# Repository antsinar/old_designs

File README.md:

Some old designs i made following tutorials online.
All KiCad projects.
The first one is a Charlie plexing keychain with a 2032 battery holder.
The second one was originally an alarm clock idea that simulated sunrise and sunset with a stackable design. (if ordered from JLCPCB, you would have one full set)
Do whatever you want with them.

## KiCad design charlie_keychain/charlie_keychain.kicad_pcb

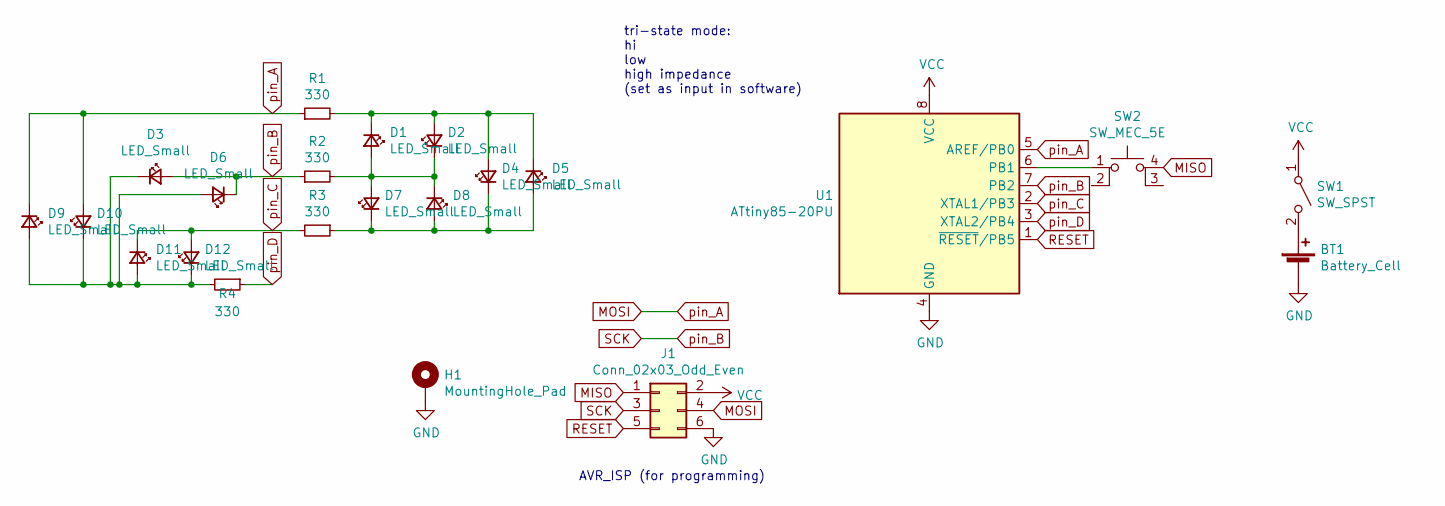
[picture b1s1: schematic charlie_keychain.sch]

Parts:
BT1: Battery_Cell; BatteryHolder_Keystone_1060_1x2032
D1, D2, D3, D4, D5, D6, D7, D8, D9, D10, D11, D12: LED_Small; LED_0805_2012Metric
H1: MountingHole_Pad; MountingHole_2.5mm_Pad_TopBottom
J1: Conn_02x03_Odd_Even; PinHeader_2x03_P2.00mm_Vertical
R1, R2, R3, R4: 330; R_0805_2012Metric
SW1: SW_SPST; SW_DIP_SPSTx01_Slide_Copal_CHS-01B_W7.62mm_P1.27mm
SW2: SW_MEC_5E; SW_SPST_Omron_B3FS-100xP
U1: ATtiny85-20PU; DIP-8_W7.62mm

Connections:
GND: BT1.2 (-), H1.1, J1.6, U1.4 (GND)
MISO: J1.1, SW2.4 (A)
MOSI: D9.1 (K), D10.2 (A), J1.4, R1.1, U1.5 (AREF/PB0)
unnamed: BT1.1 (+), SW1.2 (B)
unnamed: D1.1 (K), D2.2 (A), D4.2 (A), D5.1 (K), R1.2
unnamed: D1.2 (A), D2.1 (K), D7.2 (A), D8.1 (K), R2.2
unnamed: D4.1 (K), D5.2 (A), D7.1 (K), D8.2 (A), R3.1
unnamed: D3.1 (K), D6.2 (A), D9.2 (A), D10.1 (K), D11.2 (A), D12.1 (K), R4.2
unnamed: SW2.1, U1.6 (PB1)
RESET: J1.5, U1.1 (~RESET~/PB5)
SCK: D3.2 (A), D6.1 (K), J1.3, R2.1, U1.7 (PB2)
VCC: J1.2, SW1.1 (A), U1.8 (VCC)
pin_C: D11.1 (K), D12.2 (A), R3.2, U1.2 (XTAL1/PB3)
pin_D: R4.1, U1.3 (XTAL2/PB4)

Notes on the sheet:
tri-state mode: hi low high impedance (set as input in software)
AVR_ISP (for programming)

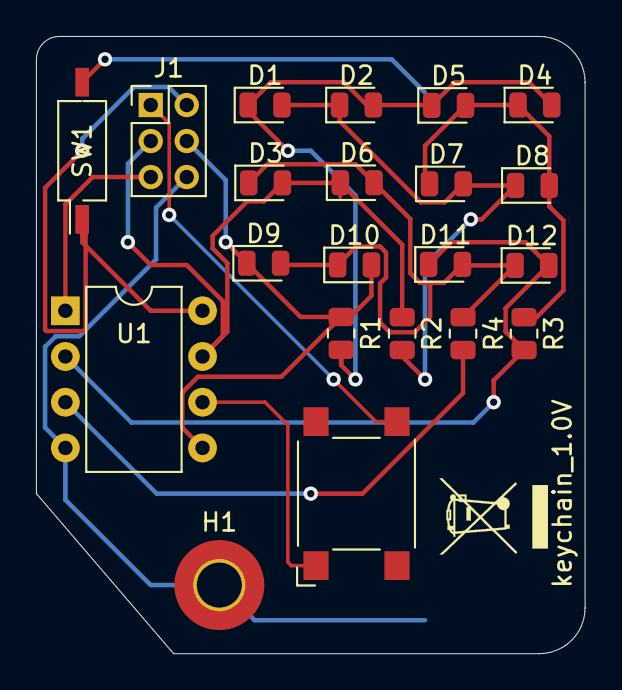
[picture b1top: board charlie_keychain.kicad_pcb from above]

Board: 2 copper layers, 30.5 x 34.3 mm, 22 parts (1 on the bottom side), 14 nets.

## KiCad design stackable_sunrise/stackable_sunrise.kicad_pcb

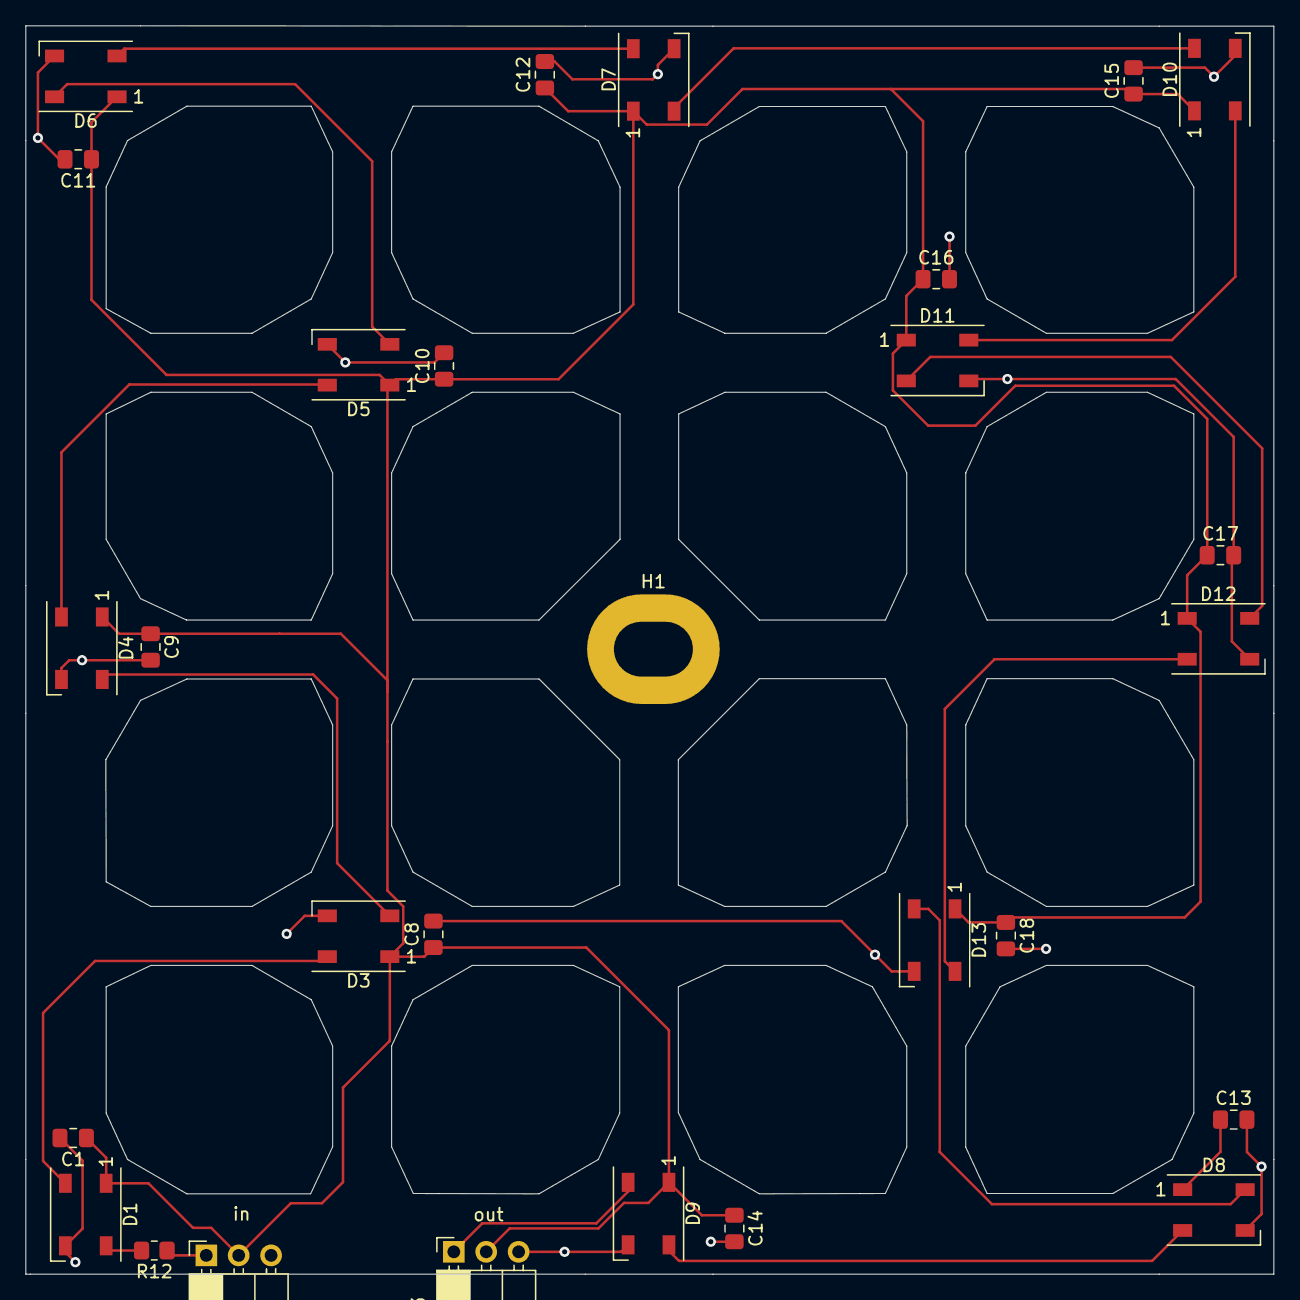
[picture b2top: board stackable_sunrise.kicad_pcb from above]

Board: 2 copper layers, 97.8 x 97.9 mm, 28 parts (0 on the bottom side), 16 nets.

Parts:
C1, C8, C9, C10, C11, C12, C13, C14, C15, C16, C17, C18: 100u; C_0805_2012Metric_Pad1.18x1.45mm_HandSolder
D1, D3, D4, D5, D6, D7, D8, D9, D10, D11, D12, D13: WS2812B; LED_WS2812B_PLCC4_5.0x5.0mm_P3.2mm
H1: MountingHole_Pad; MountingHole_4.3x6.2mm_M4_Pad
J2, J3: Conn_01x03; PinSocket_1x03_P2.54mm_Horizontal
R12: 330; R_0805_2012Metric_Pad1.20x1.40mm_HandSolder

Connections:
5v_next_layer: C1.1, C8.1, C9.1, C10.1, C11.1, C12.1, C13.1, C14.1, C15.1, C16.1, C17.1, C18.1, D1.1, D3.1, D4.1, D5.1, D6.1, D7.1, D8.1, D9.1, D10.1, D11.1, D12.1, D13.1, J2.2, J3.2
DIN: D1.4, R12.2
unnamed: D1.2, D3.4
unnamed: D3.2, D4.4
unnamed: D4.2, D5.4
unnamed: D5.2, D6.4
unnamed: D6.2, D7.4
unnamed: D8.2, D9.4
unnamed: D10.2, D11.4
unnamed: D7.2, D10.4
unnamed: D11.2, D12.4
unnamed: D12.2, D13.4
unnamed: D8.4, D13.2
unnamed: J2.1, R12.1
common_ground: C1.2, C8.2, C9.2, C10.2, C11.2, C12.2, C13.2, C14.2, C15.2, C16.2, C17.2, C18.2, D1.3, D3.3, D4.3, D5.3, D6.3, D7.3, D8.3, D9.3, D10.3, D11.3, D12.3, D13.3, H1.1, J2.3, J3.3
din_next_layer: D9.2, J3.1

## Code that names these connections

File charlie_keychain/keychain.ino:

#include <avr/sleep.h>
#define nop() asm volatile("nop")
boolean leds_on = true;

byte badly_programmed_counter = 0;
byte animation_counter_max = 5;
byte animation_counter = 0;

// we need two frames with 8 bits for 12 LEDs
byte frame1 = 0;
byte frame2 = 0;

// animation where every third LED is glowing
// I could shift that continuosly and drop 4 bytes
const byte three_apart_length = 6;
const byte three_apart[three_apart_length] PROGMEM = {
  0b10010010, 0b01000000,
  0b01001001, 0b00100000,
  0b00100100, 0b10010000,
};

// this one is huge
// is there a math function to do that instead?
const byte updown_length = 14;
const byte updown[updown_length] PROGMEM = {
  0b00100000, 0b00000000,
  0b01010000, 0b00000000,
  0b10001000, 0b00000000,
  0b00000100, 0b00010000,
  0b00000010, 0b00100000,
  0b00000001, 0b01000000,
  0b00000000, 0b10000000,
};

// that's just blinking each led 
// maybe inverting the data bitwise does the trick
const byte two_apart_length = 4;
const byte two_apart[two_apart_length] PROGMEM = {
  0b10101010, 0b10100000,
  0b01010101, 0b01010000,
};

// should have taken a switch, sleep stuff is huge
ISR(INT0_vect) {
  sleep_disable();
  leds_on = true;
}

void setup()
{
  // this is for the button setup
  PORTB |= (1 << PB1);
  DDRB &= ~(1 << PB1);

  shutdown_chip();
}

void loop()
{
  if (leds_on)
  {
    cli();
    leds_on = false;

    // I call it that, because the millis stuff
    // and the interrupts collided and broke
    badly_programmed_counter = 0;
  }

  // fancy way of checking the button state
  if (!(PINB & (1 << PB1)))
  {
    badly_programmed_counter++;
    my_100ms_delay();

    // check if button was released before time
    // so animation index can be incremented
    // maybe a modulo with animation_counter_max
    // safes space
    if ( (PINB & (1 << PB1)) )
    {
      badly_programmed_counter = 0;
      animation_counter++;
      if (animation_counter == animation_counter_max)
      {
        animation_counter = 0;
      }
      charlie(animation_counter);

      // calling a function instead of writing it down
      // 5 times helps already
      for (byte b = 0; b < 5; b++) my_100ms_delay();
    }

    if (badly_programmed_counter >= 7)
    {
      // blink when shutdown is immanent
      for (byte b = 0; b < 5; b++) blip();
      shutdown_chip();
    }
  }
  else
  {
    animate_leds();
    badly_programmed_counter = 0;
  }
}

// this is probably already at it's best
void charlie (byte var) {
  leds_off();

  switch (var) {
    case 0: // 1
      DDRB |= (1 << PB0) | (1 << PB2); // output
      PORTB |= (1 << PB0); // HIGH
      break;
    case 1: // 2
      DDRB |= (1 << PB0) | (1 << PB2); // output
      PORTB |= (1 << PB2); // HIGH
      break;
    case 2: // 3
      DDRB |= (1 << PB2) | (1 << PB3); // output
      PORTB |= (1 << PB2); // HIGH
      break;
    case 3: // 4
      DDRB |= (1 << PB2) | (1 << PB3); // output
      PORTB |= (1 << PB3); // HIGH
      break;
    case 4: // 5
      DDRB |= (1 << PB3) | (1 << PB4); // output
      PORTB |= (1 << PB3); // HIGH
      break;
    case 5: // 6
      DDRB |= (1 << PB3) | (1 << PB4); // output
      PORTB |= (1 << PB4); // HIGH
      break;
    case 6: // 7
      DDRB |= (1 << PB0) | (1 << PB3); // output
      PORTB |= (1 << PB0); // HIGH
      break;
    case 7: // 8
      DDRB |= (1 << PB0) | (1 << PB3); // output
      PORTB |= (1 << PB3); // HIGH
      break;
    case 8: // 9
      DDRB |= (1 << PB2) | (1 << PB4); // output
      PORTB |= (1 << PB2); // HIGH
      break;
    case 9: // 10
      DDRB |= (1 << PB2) | (1 << PB4); // output
      PORTB |= (1 << PB4); // HIGH
      break;
    case 10: // 11
      DDRB |= (1 << PB0) | (1 << PB4); // output
      PORTB |= (1 << PB0); // HIGH
      break;
    case 11: // 12
      DDRB |= (1 << PB0) | (1 << PB4); // output
      PORTB |= (1 << PB4); // HIGH
      break;
    default:
      ;

      nop();
  }
}

void shutdown_chip()
{
  animation_counter = 0;
  leds_off();

  /* Clear WDRF in MCUSR */
  MCUSR &= ~(1 << WDRF);
  /* Write logical one to WDCE and WDE */
  /* Keep old prescaler setting to prevent unintentional time-out */
  WDTCR |= (1 << WDCE) | (1 << WDE);
  /* Turn off WDT */
  WDTCR = 0x00;

  ADCSRA &= ~(1 << ADEN); // turn off adc

  GIMSK |= (1 << INT0);
  GIMSK |= (1 << PCIE);

  set_sleep_mode(SLEEP_MODE_PWR_DOWN);
  sleep_enable();
  sei(); // Enable global interrupts
  sleep_cpu();
  sleep_disable();
}

void animate_leds()
{
  switch (animation_counter)
  {
    case 0:
      animate_frames(
        three_apart_length,
        three_apart,
        512
      );
      break;

    case 1:
      for (byte acc_counter = 1; acc_counter < 64; acc_counter += 2)
      {
        animate_frames(
          three_apart_length,
          three_apart,
          acc_counter * 8
        );
      }
      break;

    case 2:
      animate_frames(
        updown_length,
        updown,
        512
      );
      break;

    case 3:
      animate_frames(
        two_apart_length,
        two_apart,
        2048
      );
      break;

    case 4:
      for (byte acc_counter = 1; acc_counter < 64; acc_counter += 2)
      {
        animate_frames(
          updown_length,
          updown,
          (63-acc_counter) * 4
        );
      }
      break;

    default:
      leds_off();
      break;
  }
}

void animate_frames(
  byte animation_length,
  const byte* animation_array,
  uint16_t frame_duration
) {
  for (byte i = 0; i < animation_length; i += 2)
  {
    // save the last time you blinked the LED
    frame1 = pgm_read_byte_near(animation_array + i);
    frame2 = pgm_read_byte_near(animation_array + i + 1);
    show_frame(frame_duration);
  }
}

// this just looks ugly, but needs to be done
// for loop through frame bytes to set the LEDs with 
// the charlie plex function
void show_frame(uint16_t byteframe_length)
{
  for (uint16_t j = 0; j < byteframe_length; j++)
  {
    //iterate through bit mask
    for (byte i = 0; i < 12; i++)
    {
      // if bitwise AND resolves to true
      if (
        (
          i < 8 &&
          1 << i & frame1
        ) ||
        (
          i > 7 &&
          1 << (i - 4) & frame2
        )
      )
      {
        charlie(i);
      }
      else
      {
        charlie(255);
      }
    }
  }
}

void leds_off()
{
  DDRB &= ~(0b00011101);
  PORTB &= ~(0b00011101);
}

void blip()
{
  charlie(11);
  // delay(100);
  my_100ms_delay();
  charlie(255);
  // delay(100);
  my_100ms_delay();
}

void my_100ms_delay()
{
  for (uint32_t i=0;i<40000;i++) nop();
}

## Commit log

2021-08-13 Initial Commit
    First!
